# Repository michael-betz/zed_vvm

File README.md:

# zed_vvm
A digital RF vector volt-meter (VVM).
Measures amplitude and phase of a sinusoidal signal under test against a reference signal of same frequency.
Intended as an instrument to monitor and troubleshoot legacy accelerator RF systems.

Based on a Digilent Zedboard running Debian with a DC1525A FMC daughter board on top.

  * 4 channel, 14 bit, 125 MSps, 800 MHz bandwidth (3 dB) analog to digital converter with LVDS interface: [__LTC2175-14__](https://www.analog.com/en/products/ltc2175-14.html)
  * Sampling clock provided by a `Si5xx-PROG_EVB` evaluation board running [custom firmware](https://github.com/yetifrisstlama/Si5xx-5x7-EVV_autoloader)
  * 4 x 4096 sample buffer with oscilloscope-like trigger for raw ADC waveform storage (`scope_app.py` makes use of that)
  * FPGA implements
    * digital down-conversion and decimation to get a complex baseband (IQ) signal
    * rectangular (IQ) to polar conversion (magnitude, phase)
    * first order IIR filter to smooth the measurement result
    * uses [Bedrock](https://github.com/BerkeleyLab/Bedrock) DSP blocks
    * makes good use of [litex](https://github.com/enjoy-digital/litex) Control/Status Registers (CSRs), the wishbone2axi bridge and litex_server to make the measurements available to linux running on the CPU

The main reason to choose embedded linux is the convenience for application development:
  * python3 support with numpy / scipy or even jupyter notebook
  * `sudo apt install <whatever_you_need>`
  * ssh and scp make remote access secure and easy, even on the public internet
  * remote loading of bit-files through scp is very convenient
  * litex_server can run on the zedboard, making access to CSR-registers over
    ethernet easy and transparent. The TCP connection is tunneled trough ssh,
    making it secure
  * can run epics IOC, mosquitto client or many other tools to publish
    measurement results

# Minimum design goals
  * support 125 MHz & 500 MHz signals
  * Same phase reading after power cycle (manage clock divider states)
  * 360 degree unique measurement range
  * Phase accuracy over a temperature range of 20 - 30 degC of better than 1 deg (0.2 %)
  * Less than 2 % amplitude error
  * At least 2 input channels + one phase reference channel
  * Self-contained instrument (only power is needed)
  * Easy to use
  * Not too expensive, such that it can be installed in multiple places across the facility
  * Epics support

# System block diagram

# `vvm_dsp.py` block diagram

# `phase_processor.py` block diagram

# Hardware modifications
## Zedboard
  * remove XADC header (J2) as it interferes with the DC1525A board

## DC1525A
  * Setup the board for differential sample clock input
    * Move R101 to R64 (0 Ohm jumper)
  * Remove low-pass filter on the analog input channels
    * Remove: R37, R38, R53, R54, R80, R81, R90, R91
    * Remove: R35, R52, R79, R89
    * Replace by 0 Ohm jumper: L4, L5, L6, L12

# Installing litex
... on debian
```bash
$ sudo apt install libevent-dev libjson-c-dev
$ sudo pip3 install virtualenvwrapper
$ mkvirtualenv litex
$ git clone git@github.com:yetifrisstlama/litex.git --recursive
$ cd litex
$ python litex_setup.py init
$ python litex_setup.py install
$ python setup.py develop
```

# Building the .bit file
Most of the DSP blocks are from LBLs `Bedrock` repo, which needs to be cloned
in the same directory as `zed_vvm`.

Vivado needs to be installed an in the PATH. I use v2019.1.

Setup your zedboard host-name in `util/remote_config_fpga.sh` and
`util/remote_litex_server.sh`.

Note that the Zedboard PS will freeze if the FPGA is not loaded / in the process of being loaded and there is a
AXI memory access through litex_server. So make sure to close the python apps before doing `make upload`.

```bash
$ git clone https://github.com/yetifrisstlama/zed_vvm.git
$ git clone https://github.com/BerkeleyLab/Bedrock.git
$ cd zed_vvm/gateware
$ workon litex
$ make
# remote FPGA configuration
$ make upload
# start litex_server on zedboard for remote access to FPGA registers
$ make server
# Keep this terminal open and start a new one
```

# Demo apps
[litex_server_apps](litex_server_apps/README.md)

# Setting up linux
[ZED_DEBIAN.md](linux_kernel/ZED_DEBIAN.md)

# Setting up Peripherals
How to connect Linux to the FPGA or the outside world. WIP ...

[PS_PERIPHERALS.md](linux_kernel/PS_PERIPHERALS.md)

# Load bitfile in linux
Bitfiles are loaded trough the [Linux FPGA Manager](https://www.kernel.org/doc/html/v4.18/driver-api/fpga/fpga-mgr.html).
For this to work, the .bit file needs its header removed and its bytes swapped.
This can either be done with the xilinx SDK or alternatively with `bitstream_fix.py`.
```bash
python3 util/bitstream_fix.py <bitfile>.bit
```

copy the resulting `<bitfile>.bit.bin` on the zedboard, then

```bash
    sudo -i
    cp <bitfile>.bit.bin /lib/firmware/
    echo 0 > /sys/class/fpga_manager/fpga0/flags
    echo <bitfile>.bit.bin > /sys/class/fpga_manager/fpga0/firmware
    dmesg

[ 1667.020520] fpga_manager fpga0: writing <bitfile>.bit.bin to Xilinx Zynq FPGA Manager
```

`cd gateware; make upload` tries to automate all these steps.

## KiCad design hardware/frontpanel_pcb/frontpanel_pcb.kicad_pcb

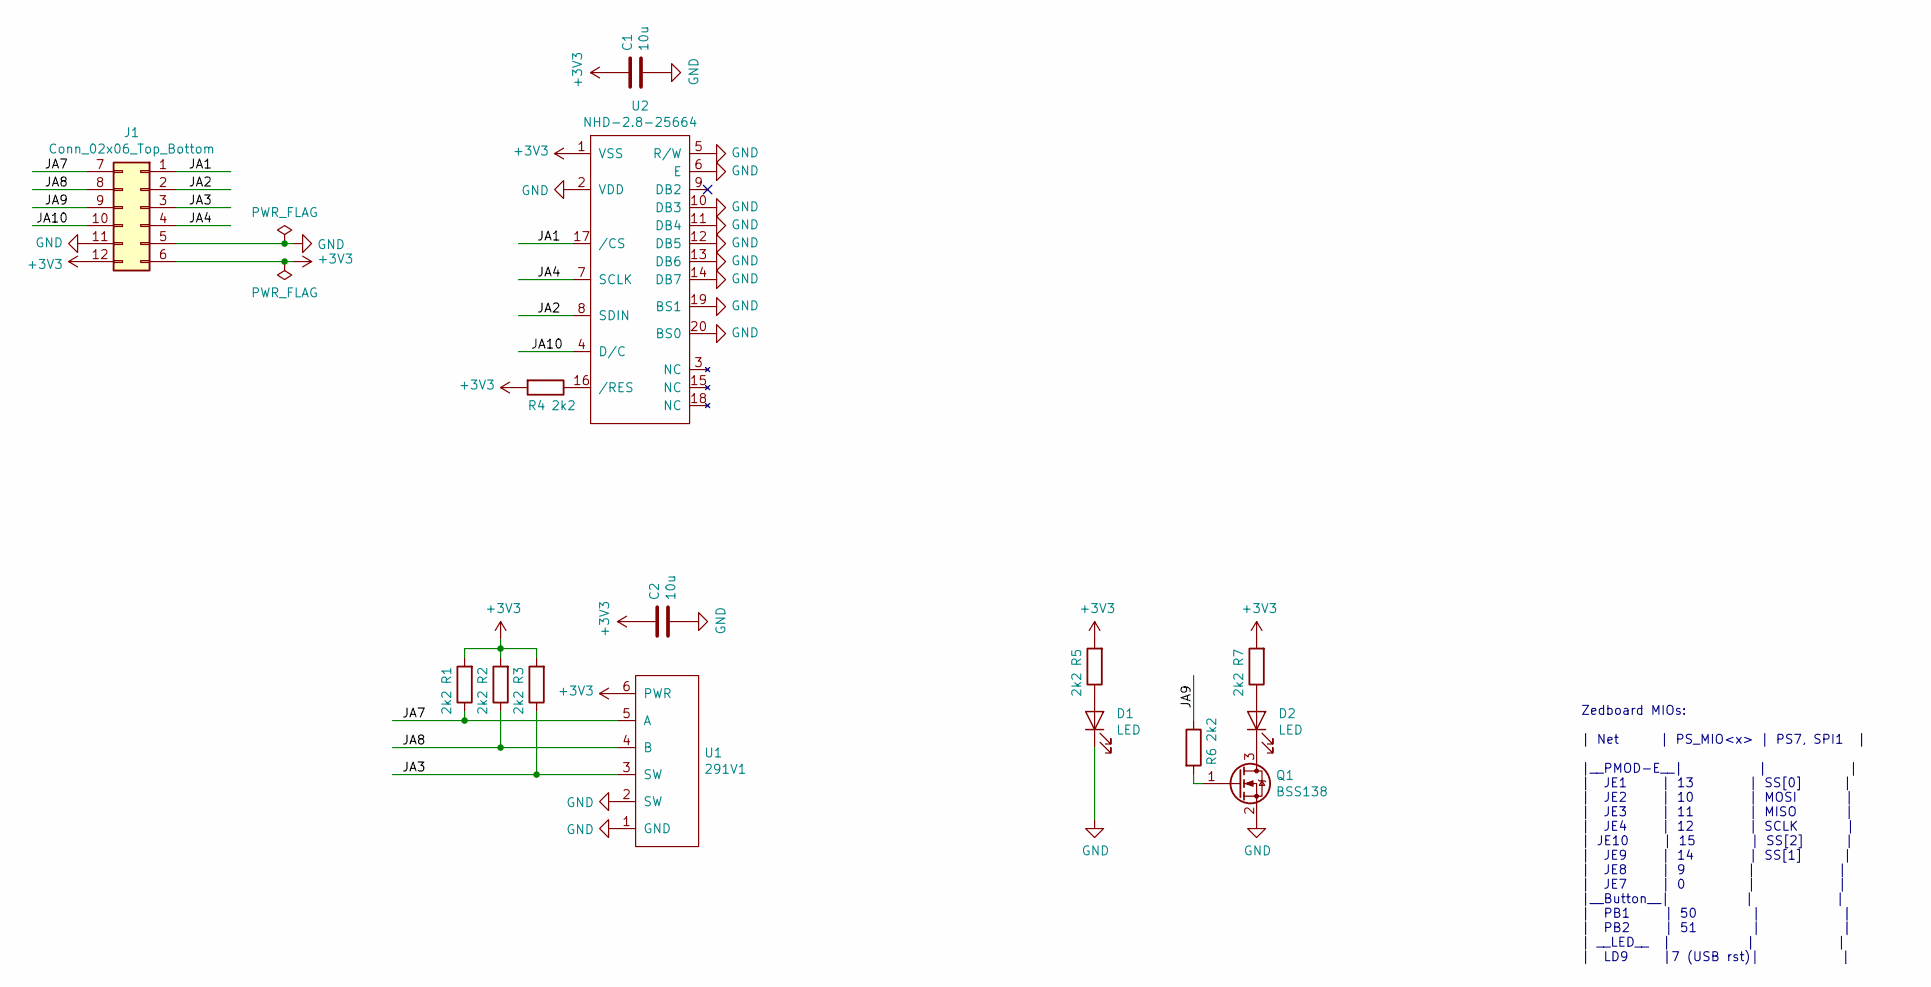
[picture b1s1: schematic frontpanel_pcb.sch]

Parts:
C1, C2: 10u; C_1206_3216Metric
D1, D2: LED; LED_D5.0mm
J1: Conn_02x06_Top_Bottom; pmod_pin_array_6x2
Q1: BSS138; SOT-23
R1, R2, R3, R4, R5, R6, R7: 2k2; R_0805_2012Metric
U1: 291V1
U2: NHD-2.8-25664; NHD-2.8-25664UCB2

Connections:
+3V3: C1.1, C2.1, J1.6, J1.12, R1.2, R2.2, R3.2, R4.2, R5.2, R7.2, U1.6 (PWR), U2.1 (VSS)
/JA1: J1.1, U2.17 (/CS)
/JA2: J1.2, U2.8 (SDIN)
/JA3: J1.3, R3.1, U1.3 (SW)
/JA4: J1.4, U2.7 (SCLK)
/JA7: J1.7, R1.1, U1.5 (A)
/JA8: J1.8, R2.1, U1.4 (B)
/JA9: J1.9, R6.1
/JA10: J1.10, U2.4 (D/C)
GND: C1.2, C2.2, D1.1 (K), J1.5, J1.11, Q1.2 (S), U1.1 (GND), U1.2 (SW), U2.2 (VDD), U2.5 (R/W), U2.6 (E), U2.10 (DB3), U2.11 (DB4), U2.12 (DB5), U2.13 (DB6), U2.14 (DB7), U2.19 (BS1), U2.20 (BS0)
unnamed: D1.2 (A), R5.1
unnamed: D2.1 (K), Q1.3 (D)
unnamed: D2.2 (A), R7.1
unnamed: Q1.1 (G), R6.2
unnamed: R4.1, U2.16 (/RES)

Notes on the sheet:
Zedboard MIOs: | Net | PS_MIO<x> | PS7, SPI1 | |__PMOD-E__| | | | JE1 | 13 | SS[0] | | JE2 | 10 | MOSI | | JE3 | 11 | MISO | | JE4 | 12 | SCLK | | JE10 | 15 | SS[2] | | JE9 | 14 | SS[1] | | JE8 | 9 | | | JE7 | 0 | | |__Button__| | | | PB1 | 50 | | | PB2 | 51 | | | __LED__ | | | | LD9 |7 (USB rst)| |

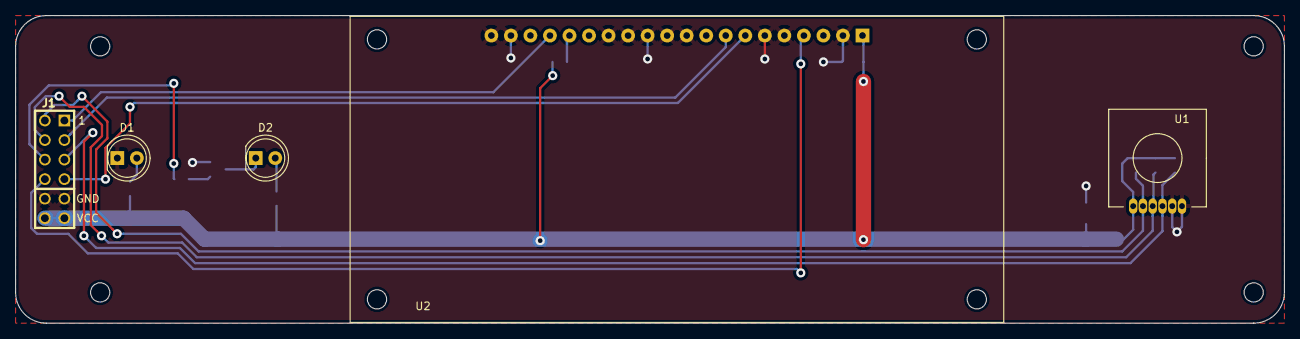
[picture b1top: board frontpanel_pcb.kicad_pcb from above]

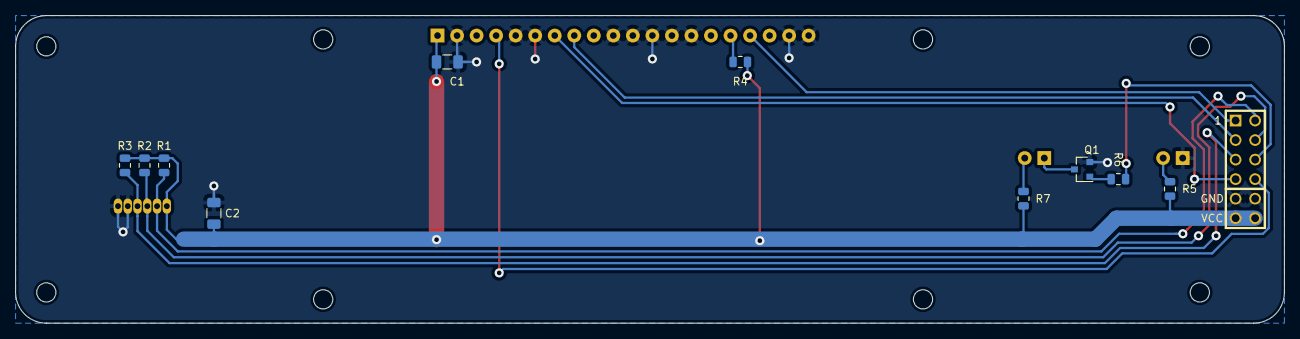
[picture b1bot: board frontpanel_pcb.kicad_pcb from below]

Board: 2 copper layers, 165.0 x 40.0 mm, 15 parts (10 on the bottom side), 15 nets.

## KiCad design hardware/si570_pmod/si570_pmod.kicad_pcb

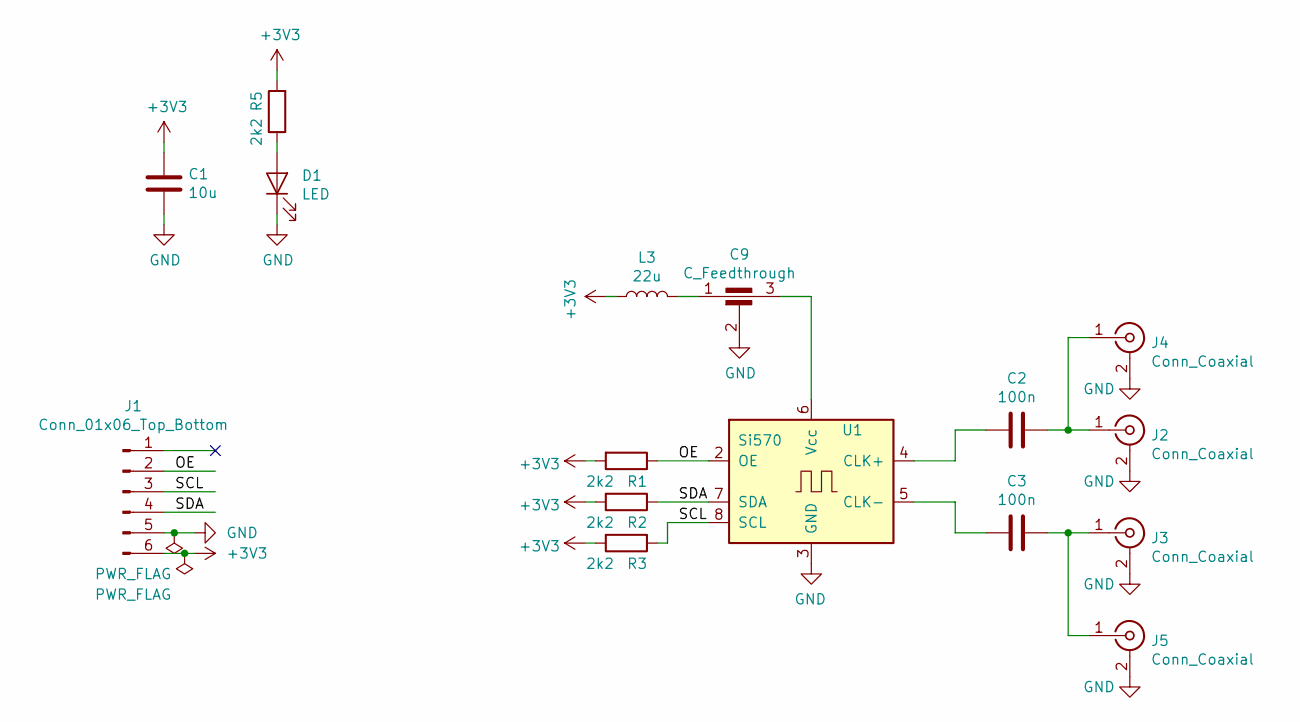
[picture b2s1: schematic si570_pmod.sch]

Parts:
C1: 10u; C_1206_3216Metric
C2, C3: 100n; C_0805_2012Metric
C9: C_Feedthrough; NFM31PC
D1: LED; LED_0805_2012Metric
J1: Conn_01x06_Top_Bottom; PinHeader_1x06_P2.54mm_Horizontal
J2, J3: Conn_Coaxial; SMA_Amphenol_132289_EdgeMount
J4, J5: Conn_Coaxial; SMA_Amphenol_132134-11_Vertical
L3: 22u; L_1210_3225Metric
R1, R2, R3, R5: 2k2; R_0805_2012Metric
U1: Si570; Oscillator_SMD_SI570_SI571_Standard

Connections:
+3V3: C1.1, J1.6, L3.1, R1.2, R2.2, R3.2, R5.2
/OE: J1.2, R1.1, U1.2 (OE)
/SCL: J1.3, R3.1, U1.8 (SCL)
/SDA: J1.4, R2.1, U1.7 (SDA)
GND: C1.2, C9.2, D1.1 (K), J1.5, J2.2 (Ext), J3.2 (Ext), J4.2 (Ext), J5.2 (Ext), U1.3 (GND)
unnamed: C2.1, J2.1 (In), J4.1 (In)
unnamed: C2.2, U1.4 (CLK+)
unnamed: C3.1, J3.1 (In), J5.1 (In)
unnamed: C3.2, U1.5 (CLK-)
unnamed: C9.1, L3.2
unnamed: C9.3, U1.6 (Vcc)
unnamed: D1.2 (A), R5.1

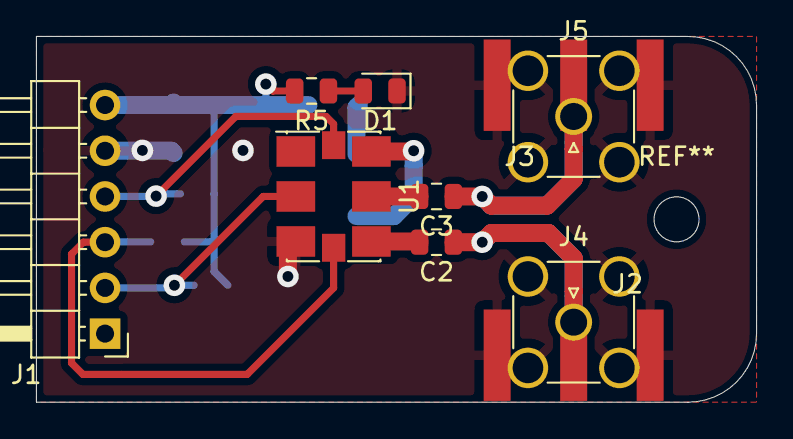
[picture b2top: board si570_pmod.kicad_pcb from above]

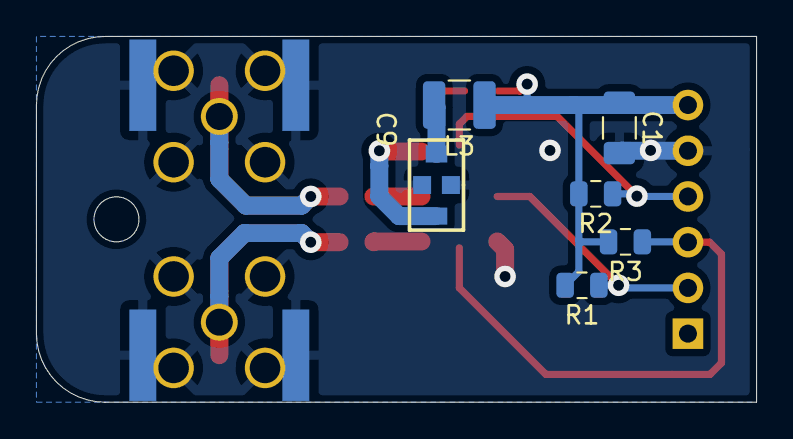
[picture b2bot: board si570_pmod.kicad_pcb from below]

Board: 2 copper layers, 40.0 x 20.3 mm, 16 parts (6 on the bottom side), 12 nets.

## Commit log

2019-10-26 initial split from litex_test_project
2019-10-26 README.md: whitespace
2019-10-26 vvm_dsp.py: add ADC_0 frequency counter
2019-10-26 docs
2019-10-26 s7_iserdes.v: remove auto-generated file
2019-10-29 add inital draft of front-panel and pcb
2019-10-30 First PCB cut
2019-10-30 directory cleanup
2019-10-30 simplified pullups
2019-10-30 might have messed up SPI pinout
2019-10-31 Streamlined .xci IP generation
2019-11-01 ip: auto_generate .xci file
    * also add EMIO SPI test
2019-11-01 zed_vvm.py: add connection from PS EMIO to hardware IO pins
2019-11-01 ZED_DEBIAN.md: note about .dts mod.
2019-11-01 frontpanel_pcb.sch: revert to pin-out as milled
2019-11-01 fix PMODA pin-out
2019-11-02 EMIO broke again
2019-11-02 ZED_DEBIAN.md add more details
2019-11-04 ZED_DEBAIN.md: update the guide
2019-11-04 zed_vvm.py: add PS SPI busses and OLED support
2019-11-05 hardware: add 2U front / back panel, add Si570 board
2019-11-05 Fix display board PMOD pinout
2019-11-05 frontpanel: update to metric, remove outdated
2019-11-05 Move a via out of the way
2019-11-06 fine-tune PCBs and FP, ordered first hardware
2019-11-06 si570_pmod: make SMA footprint milling compatible
2019-11-08 Update u-boot instruictions
2019-11-08 ZED_DEBAIN.md: add microzed
2019-11-09 ZED_DEBIAN.md: clarifications
2019-11-09 zed_debian.md: fiox path
2019-11-09 zed_debian.md: rootfs note
2019-11-09 pmod si570: add note about flipped J1
2019-11-09 Update docs, recommend stock u-boot
2019-11-09 link to PS_PERIPHERALS.md
2019-11-09 PS_PERIPHERALS.md
2019-11-10 frontpanel_pcb: change mounting holes to 2.5 mm
2019-11-12 FP notes for rev1, si570 weirdness
2019-11-13 dev sheet
2019-11-13 new i2c master
2019-11-15 fast bitbang experiment in C
2019-11-16 Rotary encoder and OLED works!
2019-11-16 Add pygame example code for oled
2019-11-16 Add linux/README
2019-11-16 clean pygame oled example
2019-11-16 add bitmap font experiment
2019-11-16 add python csr client with I2C, add .fnt lib for pygame
2019-11-17 add many python helpers for bit-banging / lvds setup
    also broke LTC SPI, swithcing it for bitbang
2019-11-18 fix SPI bit-bang driver, add CSR reset for sys_clk
2019-11-18 fix sys_clk reset, conceptual oled app
2019-11-19 vvm_oled_app.py: blank phase if magnitude is low
2019-11-20 cleanup common.py, add led to .dts
    * make csr_access compatible with litex_client (adapter class)
    * move stuff from common.py to vvm_helpers.py
    * add status led to device tree and kernel config
    * fix scope_app (Si570 setup doesnt work through litex_server)
2019-11-20 update .dts for mainline
2019-11-20 add patches to mainline to get fpga0/firmware
2019-11-20 fix .dts
2019-11-20 .config for mainline kernel
2019-11-20 add some bitmap fonts
2019-11-21 got rid of bitmap fonts
2019-11-21 zynq-zed.dts: Fix disabled FPGA clocks in mainline
2019-11-22 port ddc.v to migen, add per channel DDS
2019-11-22 docs and cleanup
2019-11-22 dsp seems broken
2019-11-22 vvm_dsp.py: fix simulation
2019-11-22 cleanup, ddc.py still buggy
2019-11-23 found dsp bug: parametr with width
2019-11-25 dds.py: make it multi-channel and synchronized
2019-11-26 add block diagram dsp.png'
2019-11-26 actually add the dsp.png
2019-11-26 add hand-drawn system block diagrm
2019-11-26 system.svg: inkscape version
2019-11-26 system.svg: typo
2019-11-26 fine tune block diags
2019-11-26 *.svg: fine tuning
2019-11-26 Readme.md
2019-11-27 ZED_DEBIAN.md: fix uEnv.txt description
2019-11-27 vvm_dsp.py: add reference phase multiplier + csr
    if a signal under test is on a harmonic frequency of the
    reference, the phasor angle from the cordic needs to be
    multiplied by the harmonic number such that small frequency
    tuning errors actually cancel out.
    This is the proof of concept implementation
    TODO rewrite the mag / phase difference calculation
2019-12-19 phase_processor.py: first stab at outsourcing the end of the pipeline
2020-01-03 fix vvm_dsp_tb.v, work on phase_processor.py
    now looking into porting everything to use stream.py
2020-01-03 Add phase_processor_tb.v
2020-01-03 phase_processor.py: implement as pipelined data path
2020-01-04 phase_processor.py: finished and integrated it!!!
2020-01-04 try to make it run. Somethings wrong with signed ints.
2020-01-04 works on hardware
    problem was a strobe which was not a pulse
2020-01-05 add phase_processor block diagram
2020-01-05 phase_processor.png: fix typo
2020-01-05 add vvm.jpg
2020-01-07 first stab at magnitude calibration over f
2020-01-07 Improve magnitude calibration
    something's wrong with channel 0 magnitude!!!
2020-01-07 digging
2020-01-08 Found CH0 problem: a cracked cap
2020-01-09 Fix CDC glitches in dds.py, finalize mag / phase calibration
    * clock domain crossing for CSR registers to the DDS controls
    was messed up / non existant. Added PulseSynchronizer.
    * Finished magnitude / phase calibration and it looks accurate!
2020-01-10 add cal to vvm_app.y
    ... now we have an input impedance match problem :(
2020-01-10 re-calibrated with 6 dB attenuators
2020-01-11 vvm_app_oled.py: make it work with cal
2020-01-11 oled service
2020-01-11 vvm_app_oled.py: worked around a nasty memory leak from evdev
2020-01-12 add vvm_daemon.py: a really sweet MQTT client for the VVM
    also added python logging
2020-01-12 update the systemd files
2020-01-12 Massive re-structuring
    Possibly broke some stuff. Also docs need to be updated now ...
2020-01-12 More massive re-structuring
2020-01-12 README.md: fix 2 links
2020-01-12 Fix some refs
2020-01-13 finalized vvm_oled.py
2020-01-13 vvm_oled.py: improve mqtt parsing
2020-01-13 vvm_oled.py: typo
2020-01-14 Make mqtt and OLED apps work on hardware
2020-01-14 inverted status led
2020-01-14 update .service files
2020-02-26 client_dev_sheet.ipynb: update import paths
2020-02-26 remote_litex_server.sh: use litex_server_light in home dir
2020-02-28 fix python apps, upgrade litex
2020-03-05 vvm_daemon.py: add Harmonic factors, fix calibration bug
2020-03-05 vvm_ioc: add trivial epics bridge
2020-03-05 vvm_daemon.py: debug
2020-03-06 vvm_daemon.py: achieved bumpless reboot ...
    DDS accumulators need to be reset after setting
    the M factors (measurement harmonic)
2020-03-06 vvm_daemon.py: add better help text
2020-03-07 vvm_dsp.py: add pulsed rf trigger logic ...
    also try to clean up the vvm_daemon.py a little
2020-03-07 bugfixes
2020-03-07 theres still some issues with pulse trigger channels
2020-03-07 mqtt_pvs.py: init order
2020-03-07 trigger still hangs on channel = 4
2020-03-07 pulsed_rf_trigger.py: remove comb to relax timing
2020-03-07 common.py: fix subversive bug in csr_helper
    also fix paths to csr.csv file in litex_server_apps/...
2020-03-09 dsp.svg: include pulsed rf trigger
2020-03-09 dsp.svg: improve
2020-07-13 small fixes to linux_apps after deploy in ALS
2020-07-13 mqtt_pvs: update some comments
2020-07-20 tiny_iir: fix acc del. by 1 cycle bug, add delay
2020-07-20 tiny_iir: synthesizer achieves better timing
2020-07-20 tini_iir: remove acc init. still has bias prbl :(
2020-07-20 linux_apps/init: add more sanity checking
2020-07-21 add trigger timeout
    * pulsed_rf_trigger: add CSR which counts trigger events
    * vvm_daemon: CW mode / only publish on new trigger event
    * vvm_oled: timeout when no new triggers come in, don't show stale
    date
    * add MultiRegs to all CsrStatus for better timing
2020-07-21 vvm_oled.py: fix mqtt bug
2020-07-21 update f_ref at 1 Hz, use time.time()
2020-07-21 vvm_helpers: add experimental clock region check
2020-07-23 vvm_oled: show mqtt parameters on oled
2020-07-25 ioc: change PV prefix
2020-07-25 bridge.py: experimental anti-drift loop
2020-07-25 bridge.py: make drift loop useable
2020-08-13 add MultiRegs on all CSR.storage
2020-08-17 litex update: fix syntax
    ... synthesizes but doesn't meet timing by -0.5 ns :( Need to investigate.
2020-08-18 s7_iserdes.py: add elastic buffers
    * add BUFG to sample clock to let placer use the full
    FPGA fabric (would only use one clock region before)
    * the global sample clock (BUFG) and the local clocks in
    each clockregion (BUFR) are now treated as asynchronous
    clock domains
    * add `ElasticBuffer` FIFOs to move data from local clocks to
2020-08-21 tried to fix a few CDC warnings
2020-10-04 add more notes to ZED_DEBIAN.md
2020-10-22 update uboot / debian instructions
2020-11-11 EPICS.md: instructions to compile and run epics
    * use qemu and chroot on a host-machine to do it quickly
    * compile and manually copy the binaries and libraries to the zedboard
    * build a demo IOC on the host-machine and copy and run it on the
    zedboard
2020-11-11 clean up EPICS instructions a bit
